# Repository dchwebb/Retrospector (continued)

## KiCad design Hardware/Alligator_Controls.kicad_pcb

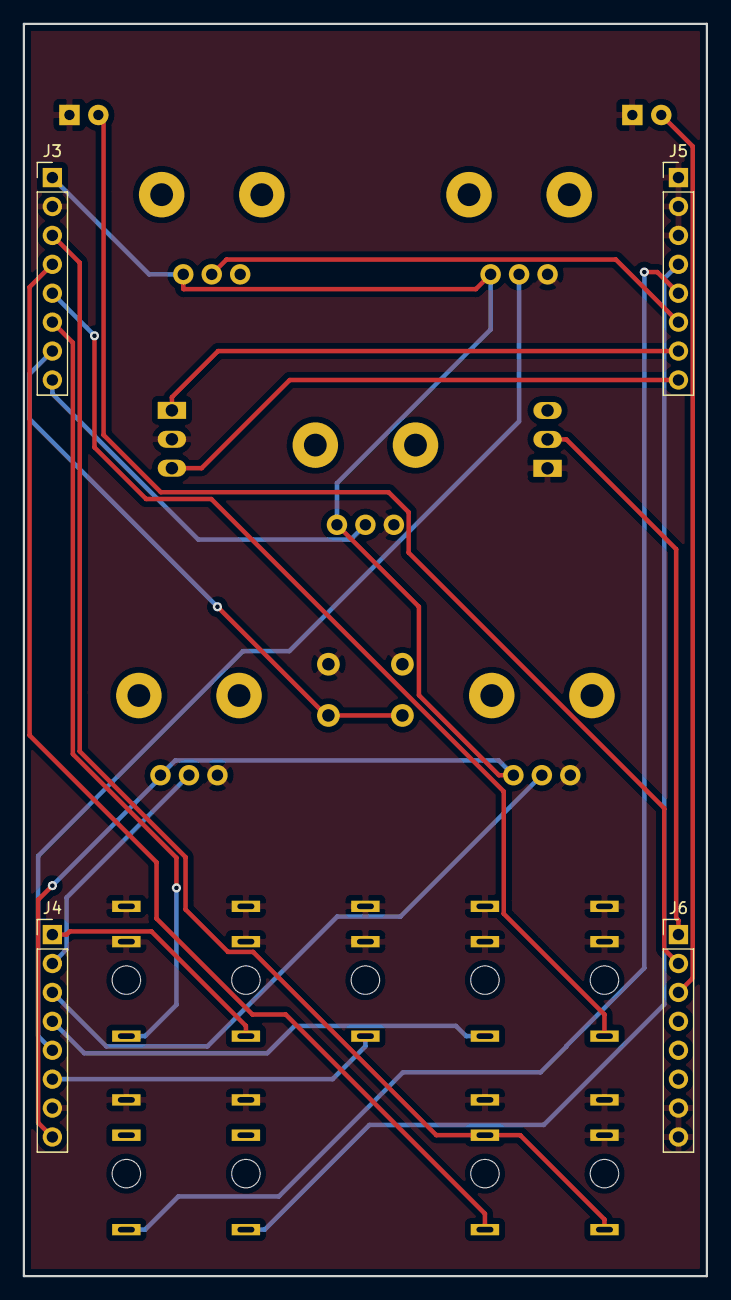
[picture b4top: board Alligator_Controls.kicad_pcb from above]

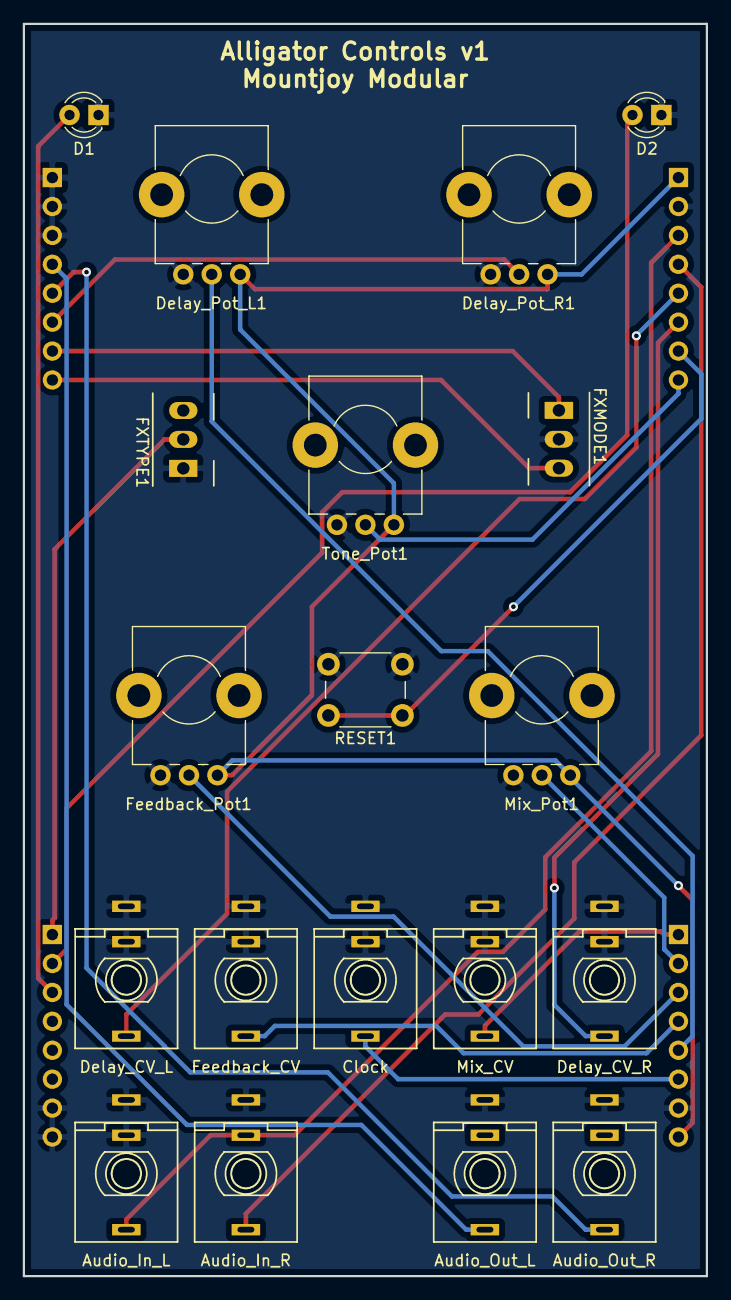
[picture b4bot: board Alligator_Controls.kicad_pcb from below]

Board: 2 copper layers, 60.0 x 110.0 mm, 23 parts (19 on the bottom side), 22 nets.

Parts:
D1, D2: LED; LED_D3.0mm
Delay_Pot_L1: A10k; Alpha_9mm_Potentiometer
Delay_Pot_R1: A10k; Alpha_9mm_Potentiometer
FXMODE1: SW_SPDT_MSM; SPDTSubMiniature
FXTYPE1: SW_SPST; SPDTSubMiniature
Feedback_Pot1: A10k; Alpha_9mm_Potentiometer
J1: Audio_In_L; THONKICONN_hole
J2: Delay_CV_L; THONKICONN_hole
J3, J4, J5, J6: Conn_01x08_Female; Socket_Strip_Straight_1x08_Pitch2.54mm
J7: Mix_CV; THONKICONN_hole
J8: Delay_CV_R; THONKICONN_hole
J9: Clock; THONKICONN_hole
J10: Feedback_CV; THONKICONN_hole
J11: Audio_In_R; THONKICONN_hole
J12: Audio_Out_R; THONKICONN_hole
J13: Audio_Out_L; THONKICONN_hole
Mix_Pot1: A10k; Alpha_9mm_Potentiometer
RESET1: SW_Push; SW_PUSH_6mm
Tone_Pot1: A10k; Alpha_9mm_Potentiometer

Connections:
+3.3VA: Delay_Pot_L1.1, Delay_Pot_R1.1, Feedback_Pot1.1, J3.1, J4.8, Mix_Pot1.1, Tone_Pot1.1
/CLOCK: J4.6, J9.3
/DELAY_CHORUS: FXTYPE1.2, J6.1
/DELAY_CV_L: J2.3, J3.5
/DELAY_CV_R: J3.6, J8.3
/DELAY_POT_L: Delay_Pot_L1.2, J4.5
/DELAY_POT_R: Delay_Pot_R1.2, J5.6
/EXT_AUDIO_IN_L: J1.3, J3.3, J11.2
/EXT_AUDIO_IN_R: J3.4, J11.3
/EXT_AUDIO_OUT_L: J5.4, J13.3
/EXT_AUDIO_OUT_R: J5.5, J12.3
/FEEDBACK_CV: J4.4, J10.3
/FEEDBACK_POT: Feedback_Pot1.2, J4.3
/LED1: D1.2, J6.3
/LED2: D2.2, J6.2
/MIX_CV: J4.1, J7.3
/MIX_POT: J4.2, Mix_Pot1.2
/MODE1: FXMODE1.1, J5.7
/MODE2: FXMODE1.3, J5.8
/RESET: J3.7, RESET1.1
/TONE_POT: J3.8, Tone_Pot1.2
GND: D1.1, D2.1, Delay_Pot_L1.3, Delay_Pot_R1.3, FXMODE1.2, FXTYPE1.1, Feedback_Pot1.3, J1.1, J1.2, J2.1, J2.2, J3.2, J4.7, J5.1, J5.2, J5.3, J6.7, J6.8, J7.1, J7.2, J8.1, J8.2, J9.1, J9.2, J10.1, J10.2, J11.1, J12.1, J13.1, Mix_Pot1.3, RESET1.2, Tone_Pot1.3

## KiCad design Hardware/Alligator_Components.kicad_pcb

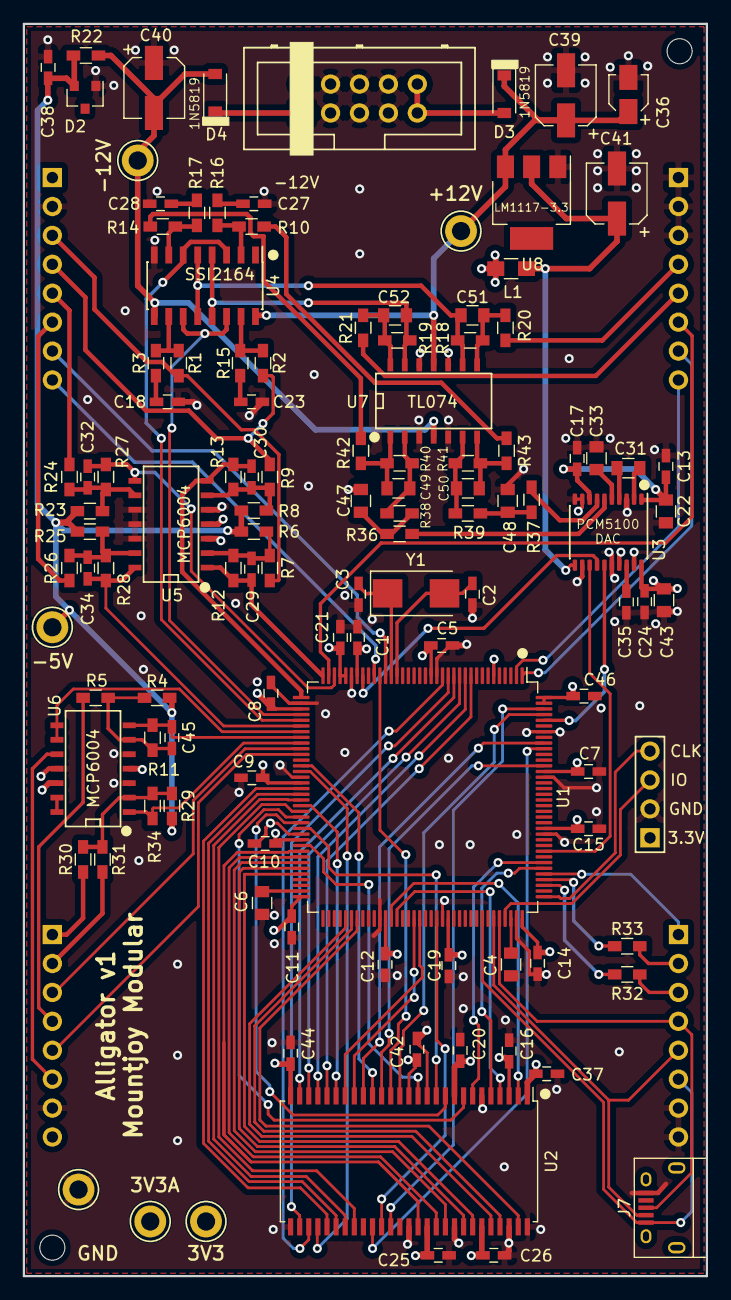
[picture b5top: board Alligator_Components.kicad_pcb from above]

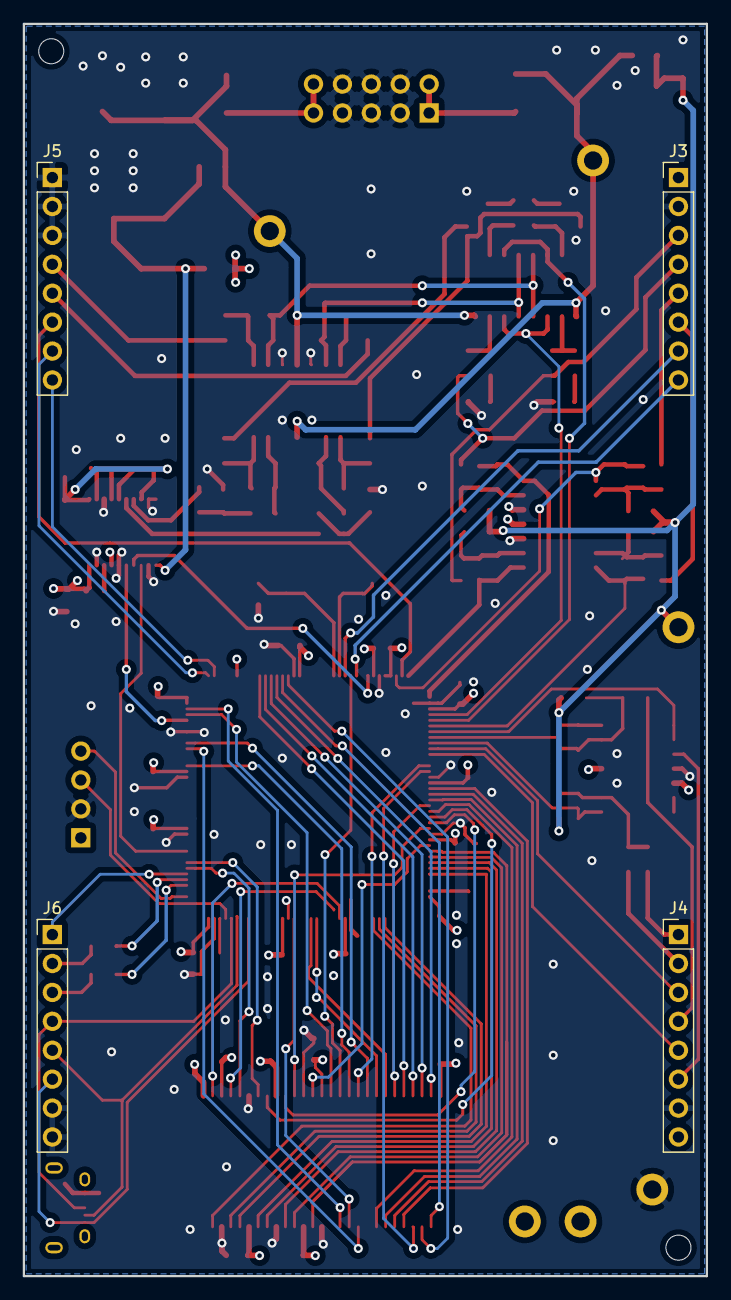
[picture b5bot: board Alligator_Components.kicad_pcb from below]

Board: 4 copper layers, 60.0 x 110.0 mm, 122 parts (4 on the bottom side), 122 nets.

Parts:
C1, C5, C7, C8, C9, C10, C11, C12, C13, C14, C15, C16, C17, C19, C20, C21, C24, C25, C26, C35, C37, C38, C42, C44, C46: 100nF; C_0603_HandSoldering
C2, C3: 30pF; C_0603_HandSoldering
C4, C6, C31, C33: 2.2uF; C_0805
C18, C23, C27, C28: 560pF; C_0603_HandSoldering
C22, C43: 10uF; C_0805
C29, C30, C32, C34, C45: 1.5nF; C_0603_HandSoldering
C36: 10uF; CP_Elec_3x5.3
C39, C40: 22uF; CP_Elec_5x5.3
C41: 47uF; CP_Elec_5x5.3
C47, C48: 1nF; C_0805
C49, C50, C51, C52: 100pF; C_0805
D2: LM4040DBZ-5; SOT-23
D3, D4: 1N5819; D_SOD-123
H1, H2: JLC_Tooling_Hole; JLC_SMT_Tooling_Hole
J1: SWD_Header; SWD_header
J2: Eurorack_10_pin_power; Eurorack_10_pin_header
J3, J4, J5, J6: Conn_01x08_Male; Pin_Header_Straight_1x08_Pitch2.54mm
J7: USB_B_Micro; USB_Micro-B_Amphenol
L1: L; L_0805_HandSoldering
R1, R2, R10, R14, R18, R19: 30k; R_0603_HandSoldering
R3, R15, R16, R17: 510R; R_0603_HandSoldering
R4, R30: 91k; R_0603_HandSoldering
R5, R24, R26: 100k; R_0603_HandSoldering
R6, R8: 20k; R_0603_HandSoldering
R7, R9, R27, R28, R31, R34: 47k; R_0603_HandSoldering
R11: 56k; R_0603_HandSoldering
R12, R13: 6k8; R_0603_HandSoldering
R20, R21, R42, R43: 1k; R_0603_HandSoldering
R22, R36, R37: 2k2; R_0603_HandSoldering
R23, R25: 68k; R_0603_HandSoldering
R29: 75k; R_0603_HandSoldering
R32, R33: 330R; R_0603_HandSoldering
R38, R39: 10k; R_0603_HandSoldering
R40, R41: 33k; R_0603_HandSoldering
TP1, TP2, TP3, TP4, TP5, TP6: TestPoint; Test_Point_Keystone_5005-5009_Compact
U1: STM32H743ZITx; LQFP-144_20x20mm_P0.5mm
U2: IS42S16400J-xC; TSOP-II-54_22.2x10.16mm_P0.8mm
U3: PCM5100APW; SSOP-20_4.4x6.5mm_Pitch0.65mm_Round_Pads
U4: SSI2164; SOIC-16_3.9x9.9mm_Pitch1.27mm
U5, U6: MCP6004; SOIC-14_N
U7: TL074; SOIC-14_N
U8: LM1117-3.3; SOT-223
Y1: 8MHz 20pF; Crystal_SMD_0603-2pin_6.0x3.5mm_HandSoldering

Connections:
+3.3VA: C13.1, C17.1, C21.2, C22.1, J3.1, J4.8, L1.1, TP3.1, U1.32, U1.33, U3.1, U3.8, U5.4, U6.4, U6.12
+3V3: C1.2, C5.2, C7.2, C8.2, C9.2, C10.2, C11.2, C12.2, C14.2, C15.2, C16.2, C19.2, C20.2, C24.1, C25.2, C26.2, C37.2, C41.1, C42.2, C43.1, C44.2, C46.2, J1.1, L1.2, TP2.1, U1.6, U1.17, U1.30, U1.39, U1.52, U1.62, U1.72, U1.84, U1.95, U1.108, U1.121, U1.131, U1.143, U1.144, U2.1, U2.3, U2.9, U2.14, U2.27, U2.43, U2.49, U3.11, U3.17, U3.20, U8.2
+12V: D3.2, J2.9, J2.10
-12V: D4.1, J2.1, J2.2
/AUDIO_IN_L: C29.1, R12.1, U1.36, U5.1
/AUDIO_IN_R: C30.1, R13.1, U1.37, U5.7
/CLOCK: J4.6, U6.10
/CLOCK_SCALED: U1.43, U6.8, U6.9
/DAC_BCLK: U1.117, U3.13
/DAC_DATA: U1.29, U3.14
/DAC_LRCLK: U1.140, U3.15
/DAC_OUT_AMP_L: R14.2, R42.1
/DAC_OUT_AMP_R: R10.2, R43.1
/DAC_OUT_L: R36.2, U3.6
/DAC_OUT_R: R37.2, U3.7
/DELAY_CHORUS: J6.1, U1.113
/DELAY_CV_L: J3.5, R24.2
/DELAY_CV_R: J3.6, R26.2
/DELAY_CV_SCALED_L: C32.1, R27.1, U1.34, U5.8
/DELAY_CV_SCALED_R: C34.1, R28.1, U1.42, U5.14
/DELAY_POT_L: J4.5, U1.47
/DELAY_POT_R: J5.6, U1.35
/DRY_OUT_L: C51.2, R18.2, U4.5, U4.12, U7.9
/DRY_OUT_R: C52.2, R19.2, U4.4, U4.13, U7.13
/EXT_AUDIO_IN_L: J3.3, R1.2, R7.2
/EXT_AUDIO_IN_R: J3.4, R2.2, R9.2
/EXT_AUDIO_OUT_L: J5.4, R20.1
/EXT_AUDIO_OUT_R: J5.5, R21.1
/FEEDBACK_CV: J4.4, R5.2
/FEEDBACK_CV_SCALED: C45.1, R11.1, U1.44, U6.7
/FEEDBACK_POT: J4.3, U1.46
/FMC_A0: U1.10, U2.23
/FMC_A1: U1.11, U2.24
/FMC_A2: U1.12, U2.25
/FMC_A3: U1.13, U2.26
/FMC_A4: U1.14, U2.29
/FMC_A5: U1.15, U2.30
/FMC_A6: U1.50, U2.31
/FMC_A7: U1.53, U2.32
/FMC_A8: U1.54, U2.33
/FMC_A9: U1.55, U2.34
/FMC_A10: U1.56, U2.22
/FMC_A11: U1.57, U2.35
/FMC_BA0: U1.89, U2.20
/FMC_BA1: U1.90, U2.21
/FMC_D0: U1.85, U2.2
/FMC_D1: U1.86, U2.4
/FMC_D2: U1.114, U2.5
/FMC_D3: U1.115, U2.7
/FMC_D4: U1.58, U2.8
/FMC_D5: U1.59, U2.10
/FMC_D6: U1.60, U2.11
/FMC_D7: U1.63, U2.13
/FMC_D8: U1.64, U2.42
/FMC_D9: U1.65, U2.44
/FMC_D10: U1.66, U2.45
/FMC_D11: U1.67, U2.47
/FMC_D12: U1.68, U2.48
/FMC_D13: U1.77, U2.50
/FMC_D14: U1.78, U2.51
/FMC_D15: U1.79, U2.53
/FMC_SDCKE1: U1.135, U2.37
/FMC_SDCLK: U1.93, U2.38
/FMC_SD~E1: U1.136, U2.19
/FMC_SD~WE: U1.26, U2.16
/FMC_~BL0: U1.141, U2.15
/FMC_~BL1: U1.142, U2.39
/FMC_~CAS: U1.132, U2.17
/FMC_~RAS: U1.49, U2.18
/LED1: J6.3, R32.1
/LED2: J6.2, R33.1
/MIX_CV: J4.1, R30.2
/MIX_DRY_CTL: U1.40, U4.11, U4.14
/MIX_POT: J4.2, R31.2
/MIX_WET_CTL: U1.41, U4.3, U4.6
/MODE1: J5.7, U1.1
/MODE2: J5.8, U1.2
/RESET: J3.7, U1.25
/SWCLK: J1.4, U1.109
/SWIO: J1.3, U1.105
/TONE_POT: J3.8, U1.27
/USB_DM: J6.5, J7.2, U1.103
/USB_DP: J6.4, J7.3, U1.104
/USB_VBUS: J6.6, J7.1, U1.101
/WET_DRY_MIX: R34.1, U1.45, U6.1
AREF_-5: C38.1, D2.2, R4.2, R6.2, R8.2, R22.2, R23.2, R25.2, R29.2, TP4.1
GND: C1.1, C2.2, C3.2, C4.2, C5.1, C6.2, C7.1, C8.1, C9.1, C10.1, C11.1, C12.1, C13.2, C14.1, C15.1, C16.1, C17.2, C18.2, C19.1, C20.1, C21.1, C22.2, C23.2, C24.2, C25.1, C26.1, C27.2, C28.2, C33.2, C35.1, C36.2, C37.1, C38.2, C39.2, C40.1, C41.2, C42.1, C43.2, C44.1, C46.1, C47.2, C48.2, D2.1, J1.2, J2.3, J2.4, J2.5, J2.6, J2.7, J2.8, J3.2, J4.7, J5.1, J5.2, J5.3, J6.7, J6.8, J7.5, TP1.1, U1.16, U1.31, U1.38, U1.51, U1.61, U1.83, U1.94, U1.107, U1.120, U1.130, U1.138, U2.6, U2.12, U2.28, U2.41, U2.46, U2.52, U2.54, U3.3, U3.9, U3.10, U3.12, U3.16, U3.19, U4.8, U5.3, U5.5, U5.10, U5.11, U5.12, U6.3, U6.5, U6.11, U7.3, U7.5, U7.10, U7.12, U8.1
unnamed: C2.1, U1.23, Y1.2
unnamed: C3.1, U1.24, Y1.1
unnamed: C4.1, U1.106
unnamed: C6.1, U1.71
unnamed: C18.1, R3.1
unnamed: C23.1, R15.1
unnamed: C27.1, R16.1
unnamed: C28.1, R17.1
unnamed: C29.2, R6.1, R7.1, R12.2, U5.2
unnamed: C30.2, R8.1, R9.1, R13.2, U5.6
unnamed: C31.1, U3.2
unnamed: C31.2, U3.4
unnamed: C32.2, R23.1, R24.1, R27.2, U5.9
unnamed: C33.1, U3.5
unnamed: C34.2, R25.1, R26.1, R28.2, U5.13
unnamed: C35.2, U3.18
unnamed: C45.2, R4.1, R5.1, R11.2, U6.6
unnamed: C47.1, R36.1, R38.2
unnamed: C48.1, R37.1, R39.2
unnamed: C49.1, R40.1, R42.2, U7.1
unnamed: C49.2, R38.1, R40.2, U7.2
unnamed: C50.1, R41.1, R43.2, U7.7
unnamed: C50.2, R39.1, R41.2, U7.6
unnamed: C51.1, R18.1, R20.2, U7.8
unnamed: C52.1, R19.1, R21.2, U7.14
unnamed: R1.1, R3.2, U4.10
unnamed: R10.1, R16.2, U4.2
unnamed: R14.1, R17.2, U4.7
unnamed: R2.1, R15.2, U4.15
unnamed: R29.1, R30.1, R31.1, R34.2, U6.2
unnamed: R32.2, U1.111
unnamed: R33.2, U1.112
unnamed: U6.13, U6.14
VCC: C36.1, C39.1, D3.1, TP5.1, U4.16, U7.11, U8.3
VEE: C40.2, D4.2, R22.1, TP6.1, U4.9, U7.4

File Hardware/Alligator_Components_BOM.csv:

"Comment","Designator","Footprint","LCSC Part #"
"100nF","C1, C5, C7, C8, C9, C10, C11, C12, C13, C14, C15, C16, C17, C19, C20, C21, C24, C25, C26, C35, C37, C38, C42, C44, C46, ","C_0603_HandSoldering","C14663"
"30pF","C2, C3, ","C_0603_HandSoldering","C22397"
"2.2uF","C4, C6, C31, C33, ","C_0805","C49217"
"560pF","C18, C23, C27, C28, ","C_0603_HandSoldering","C84721"
"10uF","C22, C43, ","C_0805","C15850 "
"1.5nF","C29, C30, C32, C34, C45, ","C_0603_HandSoldering","C1595"
"10uF","C36, ","CP_Elec_3x5.3","C249452"
"47uF","C41, ","CP_Elec_5x5.3","C134798"
"1nF","C47, C48, ","C_0805","C46653 "
"100pF","C49, C50, C51, C52, ","C_0805","C1790 "
"LM4040DBZ-5","D2, ","SOT-23","C69316"
"1N5819","D3, D4, ","D_SOD-123","C169540"
"L","L1, ","L_0805_HandSoldering","C1046"
"30k","R1, R2, R10, R14, R18, R19, ","R_0603_HandSoldering","C22984"
"510R","R3, R15, R16, R17, ","R_0603_HandSoldering","C23193"
"91k","R4, R30, ","R_0603_HandSoldering","C23265"
"100k","R5, R24, R26, ","R_0603_HandSoldering","C25803"
"20k","R6, R8, ","R_0603_HandSoldering","C4184 "
"47k","R7, R9, R27, R28, R31, R34, ","R_0603_HandSoldering","C25819"
"56k","R11, ","R_0603_HandSoldering","C23206"
"6k8","R12, R13, ","R_0603_HandSoldering","C23212 "
"1k","R20, R21, R42, R43, ","R_0603_HandSoldering","C21190"
"2k2","R22, R36, R37, ","R_0603_HandSoldering","C4190"
"68k","R23, R25, ","R_0603_HandSoldering","C23231"
"75k","R29, ","R_0603_HandSoldering","C23242 "
"330R","R32, R33, ","R_0603_HandSoldering","C23138"
"10k","R38, R39, ","R_0603_HandSoldering","C25804"
"33k","R40, R41, ","R_0603_HandSoldering","C4216 "
"STM32H743ZITx","U1, ","LQFP-144_20x20mm_P0.5mm","C114408"
"IS42S16400J-xC","U2, ","TSOP-II-54_22.2x10.16mm_P0.8mm","C69411"
"PCM5100APW","U3, ","SSOP-20_4.4x6.5mm_Pitch0.65mm_Round_Pads","C131154"
"MCP6004","U5, U6, ","SOIC-14_N","C7378"
"TL074","U7, ","SOIC-14_N","C6964"
"LM1117-3.3","U8, ","SOT-223","C6186"

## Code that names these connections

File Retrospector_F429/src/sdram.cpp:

#include <stdint.h>
#include "sdram.h"
#include "initialisation.h"

// SDRAM attached to bank 2 (ie use FMC_SDCKE1 and FMC_SDNE1 rather than 0 equivalents)

/*-- GPIOs Configuration - use Alternate Function 12
 +-------------------+--------------------+--------------------+--------------------+
 +                       SDRAM pins assignment                                      +
 +-------------------+--------------------+--------------------+--------------------+
 | PD0  <-> FMC_D2   | PE0  <-> FMC_NBL0  | PF0  <-> FMC_A0    | PG0  <-> FMC_A10   |
 | PD1  <-> FMC_D3   | PE1  <-> FMC_NBL1  | PF1  <-> FMC_A1    | PG1  <-> FMC_A11   |
 | PD8  <-> FMC_D13  | PE7  <-> FMC_D4    | PF2  <-> FMC_A2    | PG4  <-> FMC_BA0   |
 | PD9  <-> FMC_D14  | PE8  <-> FMC_D5    | PF3  <-> FMC_A3    | PG5  <-> FMC_BA1   |
 | PD10 <-> FMC_D15  | PE9  <-> FMC_D6    | PF4  <-> FMC_A4    | PG8  <-> FMC_SDCLK |
 | PD14 <-> FMC_D0   | PE10 <-> FMC_D7    | PF5  <-> FMC_A5    | PG15 <-> FMC_NCAS  |
 | PD15 <-> FMC_D1   | PE11 <-> FMC_D8    | PF11 <-> FMC_NRAS  |--------------------+
 +-------------------| PE12 <-> FMC_D9    | PF12 <-> FMC_A6    |
                     | PE13 <-> FMC_D10   | PF13 <-> FMC_A7    |
                     | PE14 <-> FMC_D11   | PF14 <-> FMC_A8    |
                     | PE15 <-> FMC_D12   | PF15 <-> FMC_A9    |
 +-------------------+--------------------+--------------------+
 | PB5 <-> FMC_SDCKE1|
 | PB6 <-> FMC_SDNE1 |
 | PC0 <-> FMC_SDNWE |
 +-------------------+
*/

void InitRamPin(GPIO_TypeDef* bank, std::initializer_list<uint8_t> pins) {
	for (auto pin : pins) {
		// Set the output speed to highest
		bank->OSPEEDR |= (0b10 << (2 * pin));		// NB 0b11 for H473

		// Set GPIO mode to alternate function (00: Input (reset state)	01: General purpose output mode	10: Alternate function mode	11: Analog mode)
		bank->MODER |= (0b10 << (2 * pin));
		bank->MODER &= ~(0b01 << (2 * pin));

		// Set alternate function to AF12
		if (pin < 8)
			bank->AFR[0] |= 12 << (4 * pin);
		else
			bank->AFR[1] |= 12 << (4 * (pin - 8));
	}
}

void InitSDRAM(void) {

	// Initialise clock for SDRAM pins
	RCC->AHB1ENR |= RCC_AHB1ENR_GPIOBEN;
	RCC->AHB1ENR |= RCC_AHB1ENR_GPIOCEN;
	RCC->AHB1ENR |= RCC_AHB1ENR_GPIODEN;
	RCC->AHB1ENR |= RCC_AHB1ENR_GPIOEEN;
	RCC->AHB1ENR |= RCC_AHB1ENR_GPIOFEN;
	RCC->AHB1ENR |= RCC_AHB1ENR_GPIOGEN;

	InitRamPin(GPIOB, {5, 6});
	InitRamPin(GPIOC, {0});
	InitRamPin(GPIOD, {0, 1, 8, 9, 10, 14, 15});
	InitRamPin(GPIOE, {0, 1, 7, 8, 9, 10, 11, 12, 13, 14, 15});
	InitRamPin(GPIOF, {0, 1, 2, 3, 4, 5, 11, 12, 13, 14, 15});
	InitRamPin(GPIOG, {0, 1, 4, 5, 8, 15});

	// Enable the SDRAM Controller
	RCC->AHB3ENR |= RCC_AHB3ENR_FMCEN;
	while (FMC_Bank5_6->SDSR & FMC_SDSR_BUSY_Msk);

	// Clock configuration - FMC clock (fmc_ker_ck) selected with RCC_D1CCIPR_FMCSEL register. Defaults to D1 domain AHB prescaler (RCC_D1CFGR_HPRE_3) ie main clock /2 = 140MHz
	//RCC->D1CCIPR |= RCC_D1CCIPR_FMCSEL_1;					// 10: pll2_r_ck clock selected as kernel peripheral clock (286MHz)

	// Memory maximum clock speed is 140MHz at CAS latency = 3

	// SDCLK, RPIPE, RBURST in Control register and TRP, TRC in Timing register are shared and must be configured against bank 1 even though using bank 2
	FMC_Bank5_6->SDCR[0] = FMC_SDCR1_RPIPE_0 |				// Read pipe: 01: One HCLK clock cycle delay
			               FMC_SDCR1_RBURST |				// Burst read: 1: single read requests are always managed as bursts
	                       FMC_SDCR1_SDCLK_1;				// SDRAM clock configuration 10: SDCLK period = 2 x HCLK periods (@180MHz = 5.55ns period; 2 x period = 11.1ns)

	FMC_Bank5_6->SDCR[1] = FMC_SDCR2_CAS_Msk |				// CAS Latency in number of memory clock cycles: 11: 3 cycles
	                       FMC_SDCR2_NB |					// Number of internal banks: 1: Four internal Banks (2M x16 x4 Banks)
	                       FMC_SDCR2_MWID_0 |				// Memory data bus width.	00: 8 bits	01: 16 bits	10: 32 bits
	                       FMC_SDCR2_NR_0 |					// Number of row address bits 01: 12 bits = 4096 - See RAM datasheet p2 Device Overview
						   FMC_SDCR2_NC_0;					// Number of column address bits 01: 9 bits = 512

	// ISSI IS42S16800 SDRAM Timings on p17 of datasheet. All settings below in cycles minus one
	FMC_Bank5_6->SDTR[0] = 2 << FMC_SDTR1_TRP_Pos |			// Row precharge delay - requires 15ns (3 cycles)
	                       5 << FMC_SDTR1_TRC_Pos;			// Row Cycle Delay - requires 60ns (6 cycles) in data sheet: trc Command Period (REF to REF / ACT to ACT)

	FMC_Bank5_6->SDTR[1] = 2 << FMC_SDTR2_TRCD_Pos |		// Row to column delay - requires 15ns (3 cycles)
	                       2 << FMC_SDTR2_TWR_Pos |			// Write Recovery Time - requires 14ns (3 cycles) - in dataheet Input Data To Precharge/Command Delay time
	                       3 << FMC_SDTR2_TRAS_Pos |		// Self Refresh Time - minimum 37ns (4 cycles)
	                       6 << FMC_SDTR2_TXSR_Pos |		// Exit Self Refresh Time - 67ns (7 cycles)
	                       2 << FMC_SDTR2_TMRD_Pos;			// Load to Active Delay - requires 14ns (3 cycles)

	// p1664  Set MODE to 001 and configure Target Bank 2 to start delivering the clock to the memory (SDCKE is driven high)
	while (FMC_Bank5_6->SDSR & FMC_SDSR_BUSY_Msk);
	FMC_Bank5_6->SDCMR = FMC_SDCMR_CTB2 | 0b001 << FMC_SDCMR_MODE_Pos;		// Command target bank 2 | Clock enable command

	// sleep at least 100uS
	uint32_t time = SysTickVal;
	while (time == SysTickVal) {};

	// Set MODE to 010 and configure Target Bank 2 to issue a "Precharge All" command
	while (FMC_Bank5_6->SDSR & FMC_SDSR_BUSY_Msk);
	FMC_Bank5_6->SDCMR = FMC_SDCMR_CTB2 | 0b010 << FMC_SDCMR_MODE_Pos;		// Command target bank 2 | Precharge All command

	// Set MODE to 011 to configure number of consecutive Auto-refresh commands (NRFS) in the FMC_SDCMR register. Typical number is 8
	while (FMC_Bank5_6->SDSR & FMC_SDSR_BUSY_Msk);
	FMC_Bank5_6->SDCMR = FMC_SDCMR_CTB2 |					// Command target bank (bank 2)
						 0b011 << FMC_SDCMR_MODE_Pos |		// Auto refresh command
						 3 << FMC_SDCMR_NRFS_Pos;			// Number of auto-refresh less one (ie 4)

	// These parameters are specified in the SDRAM datasheet (p19 for ISSI SDRAM)
	#define SDRAM_MODE_BURST_LENGTH_1				((uint16_t)0x0000)
	#define SDRAM_MODE_BURST_LENGTH_2				((uint16_t)0x0001)
	#define SDRAM_MODE_BURST_LENGTH_4				((uint16_t)0x0002)
	#define SDRAM_MODE_BURST_LENGTH_8				((uint16_t)0x0004)
	#define SDRAM_MODE_BURST_TYPE_SEQUENTIAL		((uint16_t)0x0000)
	#define SDRAM_MODE_BURST_TYPE_INTERLEAVED		((uint16_t)0x0008)
	#define SDRAM_MODE_CAS_LATENCY_2				((uint16_t)0x0020)
	#define SDRAM_MODE_CAS_LATENCY_3				((uint16_t)0x0030)
	#define SDRAM_MODE_OPERATING_MODE_STANDARD		((uint16_t)0x0000)
	#define SDRAM_MODE_WRITEBURST_MODE_PROGRAMMED	((uint16_t)0x0000)
	#define SDRAM_MODE_WRITEBURST_MODE_SINGLE		((uint16_t)0x0200)

	// Set MODE to 100 to issue a "Load Mode Register" command in order to program the SDRAM
	uint32_t tr_tmp = SDRAM_MODE_BURST_LENGTH_4 |		// was SDRAM_MODE_BURST_LENGTH_2
				SDRAM_MODE_BURST_TYPE_SEQUENTIAL |
				SDRAM_MODE_CAS_LATENCY_3 |
				SDRAM_MODE_OPERATING_MODE_STANDARD |
				SDRAM_MODE_WRITEBURST_MODE_SINGLE;

	while (FMC_Bank5_6->SDSR & FMC_SDSR_BUSY_Msk);
	FMC_Bank5_6->SDCMR = FMC_SDCMR_CTB2 |					// Command target bank (bank 2)
						 0b100 << FMC_SDCMR_MODE_Pos |		// Clock enable command
						 tr_tmp << FMC_SDCMR_MRD_Pos;		// Mode register direction

	// Set the refresh counter to trigger an auto refresh often enough to prevent data loss.
	FMC_Bank5_6->SDRTR = 683 << FMC_SDRTR_COUNT_Pos;

	// 16 megabytes of ram now available at address 0xD0000000 - 0xD1000000
}

// SDRAM testing variables
using memSize = uint32_t;
uint32_t testAddr;
memSize* tempAddr;
constexpr uint32_t maxAddr = 0x1000000 / sizeof(memSize);
uint32_t MemTestDuration;
uint32_t MemTestCount = 0;
uint32_t MemTestErrors = 0;

// Tell linker script to store buffer in SDRAM
uint32_t __attribute__((section (".sdramSection"))) SDRAMBuffer[maxAddr];

// Test SDRAM
void MemoryTest() {
	static uint32_t memErrs = 0;
	uint32_t testStart = SysTickVal;

	// Blank Memory
	GPIOC->ODR |= GPIO_ODR_OD11;			// Toggle LED for testing
	for (testAddr = 0; testAddr < maxAddr; ++testAddr) {
		tempAddr = (memSize *)(0xD0000000 + (testAddr * sizeof(memSize)));
		*tempAddr = 0;
	}
	GPIOC->ODR &= ~GPIO_ODR_OD11;

	// Write
	for (testAddr = 0; testAddr < maxAddr; ++testAddr) {
		tempAddr = (memSize *)(0xD0000000 + (testAddr * sizeof(memSize)));
		*tempAddr = static_cast<memSize>(testAddr);

	}

	// Read
	for (testAddr = 0; testAddr < maxAddr; ++testAddr) {
		memSize val = SDRAMBuffer[testAddr];
		if (val != static_cast<memSize>(testAddr))
			++memErrs;
	}

	// H743: For 32 bit words > 6632 using PLL2 at 143MHz, 6309 at 220MHz, 6385 (2813 with DCache, 2347 with DCache and ICache) at 100MHz
	// F429: 32 bit words: 180MHz 2975

	MemTestDuration = SysTickVal - testStart;
	++MemTestCount;
	MemTestErrors = memErrs;
}

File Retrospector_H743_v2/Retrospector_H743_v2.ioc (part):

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Mcu.Name=STM32H743ZITx
Mcu.Package=LQFP144
Mcu.UserName=STM32H743ZITx
PA11.Mode=Device_Only
PA11.Signal=USB_OTG_FS_DM
PA12.Mode=Device_Only
PA12.Signal=USB_OTG_FS_DP
PA4.Signal=ADCx_INP18
PA5.Signal=COMP_DAC12_group
PA7.Signal=FMC_SDNWE
PA8.Mode=Activate_SOF_FS
PA8.Signal=USB_OTG_FS_SOF
PA9.Mode=Activate_VBUS
PA9.Signal=USB_OTG_FS_VBUS
PB0.GPIOParameters=GPIO_Label
PB0.GPIO_Label=LD1 [Green Led]
PB0.Signal=GPIO_Output
PB13.Mode=Half_Duplex_Master_Tx
PB13.Signal=I2S2_CK
PB14.GPIOParameters=GPIO_Label
PB14.GPIO_Label=LD3 [Red Led]
PB14.Signal=GPIO_Output
PB15.Mode=Half_Duplex_Master_Tx
PB15.Signal=I2S2_SDO
PB5.Mode=SdramChipSelect2_2
PB5.Signal=FMC_SDCKE1
PB6.Mode=SdramChipSelect2_2
PB6.Signal=FMC_SDNE1
PB7.GPIOParameters=GPIO_Pu
PB7.GPIO_Pu=GPIO_PULLUP
PB7.Mode=I2C
PB7.Signal=I2C1_SDA
PB8.GPIOParameters=GPIO_Pu
PB8.GPIO_Pu=GPIO_PULLUP
PB8.Mode=I2C
PB8.Signal=I2C1_SCL
PB9.Mode=Half_Duplex_Master_Tx
PB9.Signal=I2S2_WS
PC0.Signal=ADCx_INP10
PC13.GPIOParameters=GPIO_Label
PC13.GPIO_Label=B1 [Blue PushButton]
PC13.Signal=GPIO_Input
PC14-OSC32_IN\ (OSC32_IN).Mode=LSE-External-Oscillator
PC14-OSC32_IN\ (OSC32_IN).Signal=RCC_OSC32_IN
PC15-OSC32_OUT\ (OSC32_OUT).Mode=LSE-External-Oscillator
PC15-OSC32_OUT\ (OSC32_OUT).Signal=RCC_OSC32_OUT
PD0.Signal=FMC_D2_DA2
PD1.Signal=FMC_D3_DA3
PD10.Signal=FMC_D15_DA15
PD14.Signal=FMC_D0_DA0
PD15.Signal=FMC_D1_DA1
PD8.Signal=FMC_D13_DA13
PD9.Signal=FMC_D14_DA14
PE0.Signal=FMC_NBL0
PE1.Signal=FMC_NBL1
PE10.Signal=FMC_D7_DA7
PE11.Signal=FMC_D8_DA8
PE12.Signal=FMC_D9_DA9
PE13.Signal=FMC_D10_DA10
PE14.Signal=FMC_D11_DA11
PE15.Signal=FMC_D12_DA12
PE7.Signal=FMC_D4_DA4
PE8.Signal=FMC_D5_DA5
PE9.Signal=FMC_D6_DA6
PF0.Signal=FMC_A0
PF1.Signal=FMC_A1
PF11.Signal=FMC_SDNRAS
PF12.Signal=FMC_A6
PF13.Signal=FMC_A7
PF14.Signal=FMC_A8
PF15.Signal=FMC_A9
PF2.Signal=FMC_A2
PF3.Signal=FMC_A3
PF4.Signal=FMC_A4
PF5.Signal=FMC_A5
PF7.Mode=TX_Only_Simplex_Unidirect_Master
PF7.Signal=SPI5_SCK
PF9.Mode=TX_Only_Simplex_Unidirect_Master
PF9.Signal=SPI5_MOSI
PG0.Signal=FMC_A10
PG1.Signal=FMC_A11
PG15.Signal=FMC_SDNCAS
PG2.Signal=FMC_A12
PG4.Signal=FMC_A14_BA0
PG5.Signal=FMC_A15_BA1
PG7.GPIOParameters=GPIO_Label
PG7.GPIO_Label=USB_OTG_FS_OVCR
PG7.Signal=GPXTI7
PG8.Signal=FMC_SDCLK
PH0-OSC_IN\ (PH0).Mode=HSE-External-Oscillator
PH0-OSC_IN\ (PH0).Signal=RCC_OSC_IN
PH1-OSC_OUT\ (PH1).Mode=HSE-External-Oscillator
PH1-OSC_OUT\ (PH1).Signal=RCC_OSC_OUT
RCC.HSE_VALUE=8000000
RCC.SYSCLKFreq_VALUE=400000000
RCC.SYSCLKSource=RCC_SYSCLKSOURCE_PLLCLK
board=NUCLEO-H743ZI2
boardIOC=true

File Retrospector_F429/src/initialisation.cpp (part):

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
void InitDAC()
{
	// DAC1_OUT2 on PA5
	RCC->AHB1ENR |= RCC_AHB1ENR_GPIOAEN;			// GPIO port clock
	RCC->APB1ENR |= RCC_APB1ENR_DACEN;			// Enable DAC Clock

	DAC->CR |= DAC_CR_EN1;							// Enable DAC using PA4 (DAC_OUT1)
	DAC->CR |= DAC_CR_BOFF1;						// Enable DAC channel output buffer to reduce the output impedance
	DAC->CR |= DAC_CR_TEN1;							// DAC 1 enable trigger
	DAC->CR |= DAC_CR_TSEL1;						// Set trigger to software (0b111: Software trigger)

	DAC->CR |= DAC_CR_EN2;							// Enable DAC using PA5 (DAC_OUT2)
	DAC->CR |= DAC_CR_BOFF2;						// Enable DAC channel output buffer
	DAC->CR |= DAC_CR_TEN2;							// DAC 2 enable trigger
	DAC->CR |= DAC_CR_TSEL2;						// Set trigger to software (0b111: Software trigger)
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
	/*--------------------------------------------------------------------------------------------
	Configure ADC Channels to be converted:
		0	PA2 ADC12_INP14		AUDIO_IN_L
		1	PA3 ADC12_INP15 	AUDIO_IN_R
		2	PC5 ADC12_INP8		WET_DRY_MIX
		3	PB1 ADC12_INP5		DELAY_POT_L
		4	PA1 ADC1_INP17		DELAY_POT_R
		5	PA0 ADC1_INP16		DELAY_CV_SCALED_L
		6	PA6 ADC12_INP3 		DELAY_CV_SCALED_R
		7	PB0 ADC12_INP9		FEEDBACK_POT
		8	PC4 ADC12_INP4		FEEDBACK_CV_SCALED
		9	PC1 ADC123_INP11 	TONE_POT
	*/

	// NB reset mode of GPIO pins is 0b11 = analog mode so shouldn't need to change
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
	/*--------------------------------------------------------------------------------------------
	Configure ADC Channels to be converted:
		0	PA2 ADC12_INP2		AUDIO_IN_L
		1	PA3 ADC12_INP3 		AUDIO_IN_R
		2	PC5 ADC12_INP15		WET_DRY_MIX
		3	PB1 ADC12_INP9		DELAY_POT_L
		4	PA1 ADC1_INP1		DELAY_POT_R
		5	PA0 ADC1_INP0		DELAY_CV_SCALED_L
		6	PA6 ADC12_INP6 		DELAY_CV_SCALED_R
		7	PB0 ADC12_INP8		FEEDBACK_POT
		8	PC4 ADC12_INP14		FEEDBACK_CV_SCALED
		9	PC1 ADC123_INP11 	TONE_POT
	*/
	InitAdcPin(GPIOA, 2, 2);
	InitAdcPin(GPIOA, 3, 3);
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	RCC->AHB1ENR |= RCC_AHB1ENR_GPIODEN;			// GPIO port clock
	RCC->APB1ENR |= RCC_APB1ENR_SPI2EN;

	// PB9: I2S2_WS [alternate function AF5]
	GPIOB->MODER |= GPIO_MODER_MODE9_1;				// 10: Alternate function mode
	GPIOB->AFR[1] |= 5 << GPIO_AFRH_AFSEL9_Pos;		// Alternate Function 5 (I2S2)

	// PD3 I2S2_CK [alternate function AF5]
	GPIOD->MODER |= GPIO_MODER_MODE3_1;				// 00: Input (reset state)	01: General purpose output mode	10: Alternate function mode	11: Analog mode
	GPIOD->AFR[0] |= 5 << GPIO_AFRL_AFSEL3_Pos;		// Alternate Function 5 (I2S2)

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
void InitTempoClock()
{
	// Fire interrupt when clock pulse is received on PA7 - See manual p383
	RCC->AHB1ENR |= RCC_AHB1ENR_GPIOAEN;			// GPIO port clock
	GPIOA->MODER &= ~GPIO_MODER_MODE7_Msk;			// 00: Input mode
	SYSCFG->EXTICR[1] |= SYSCFG_EXTICR2_EXTI7_PA;	// Select Pin PA7 which uses External interrupt 2
	EXTI->RTSR |= EXTI_RTSR_TR7;					// Enable rising edge trigger
	EXTI->IMR |= EXTI_IMR_IM7;					// Activate interrupt using mask register

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{
	// Configure timer to use Capture and Compare mode on external clock to time duration between pulses (not using)

	// FIXME Production will use PA7 - temporarily using PB5 as also configured as TIM3_CH2
	// See manual page 1670 for info on Capture and Compare Input mode
	RCC->AHB1ENR |= RCC_AHB1ENR_GPIOBEN;			// GPIO port clock
	GPIOB->MODER &= ~GPIO_MODER_MODE5_0;			// Alternate function is Mode 0b10 (defaults to 0b11)
	GPIOB->AFR[0] |= 2 << GPIO_AFRL_AFSEL5_Pos;		// Alternate Function 2 for TIM3_CH2 on PB5 and PA7
	RCC->APB1ENR |= RCC_APB1ENR_TIM3EN;
	TIM3->ARR = 65535;
	TIM3->PSC = 2000;
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
void InitLEDs()
{
	// Initialise timing LEDs on PC10 and PC11
	RCC->AHB1ENR |= RCC_AHB1ENR_GPIOCEN;			// GPIO port clock
	GPIOC->MODER |= GPIO_MODER_MODE10_0;			// 00: Input (reset state)	01: General purpose output mode	10: Alternate function mode	11: Analog mode
	GPIOC->MODER |= GPIO_MODER_MODE11_0;			// 00: Input (reset state)	01: General purpose output mode	10: Alternate function mode	11: Analog mode
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
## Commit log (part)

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2020-06-26 First draft of VCOM UART functionality - basics working but RX interrupt not clearing
2020-06-27 Fixed issues switching to high speed mode; USART working
2020-06-28 Provisional ADC code
2020-06-30 Rough first draft of ADC with DMA code (working)
2020-06-30 Added multiple ADC channels and oversampling
2020-07-02 First working draft of I2S DAC controller
2020-07-02 I2S Code working
2020-07-07 Updates to schematic; Output ADC data over I2S via interrupt with L/R awareness
2020-07-08 Basic variable delay implemented
2020-07-09 Preliminary attempts at crossfading when changing delay time
2020-07-10 Refactoring
2020-07-10 Moved delay functionality to digitalDelay class; further working smoothing delay rate transitions
2020-08-18 Added working USB Device code (mainly borrowed from MIDI Monger for testing); also updated UART debugging code
2020-08-21 UART Cleanup
2020-09-03 Attempt to identify zero crossing poinst when changing delay times (too slow)
2020-09-04 Delay change implemented on matching crossing - still not sounding right
2020-09-07 Added initialisation and test code for DAC output; Schematic changes for first attempt at Wet/Dry mixer
2020-09-08 Implemented Wet/Dry mix control using MCU to process curves
2020-09-09 Updates to schematic
2020-09-11 First Draft of Component Schematic Done; Added enum for ADC input selction
2020-09-14 Initial pass at routing MCU and DRAM
2020-09-15 Further routing of PCB
2020-09-17 Further updates to pcb layout
2020-09-18 Error pass of schematic and PCB - power rails still need routing
2020-09-18 Completed PCB routing
2020-09-30 Tooling holes added for SMT assembly; started routing control PCB
2020-10-01 More controls routing
2020-10-01 Control PCB orientation tests
2020-10-06 Renamed project files; work on panel PCB and 3d Models
2020-10-08 Added some test clock code using timer to capture clock interval in capture and compare input mode
2020-10-08 Added Clock on interrupt method
2020-10-15 Final changes to PCBs for manufacture
2020-10-30 Pre-migration to production prototype board
2020-10-31 Updated ADC conversions to match prototype board
2020-11-10 Fixed USB (Enable VDD33USB supply level detector)
2020-11-13 SDRAM working with basic tests
2020-11-13 Memory tests refined to allow easy benchmarking of different word sizes
2020-11-14 Updated SDRAM controller to use PLL2R for clock; moved memory tests to separate routine for timing testing
2020-11-15 Experiments with memory timing (currently working at 100MHz); tests with instruction and data cache; attempt to disable data cache for ADC (not working)
2020-11-16 MPU working correctly - data and instruction cache are enabled generally; data cache disabled for ADC DMA buffer
2020-11-20 Started adding circuitry for Buck conversion
2020-11-22 Added Buck converter to PCB; other layout changes
2020-11-23 Completed draft of rev 2 pcb
2020-11-23 Include inverting op amp output stage so output is not polarity reversed
2020-11-25 Created Power Test Board for TPS5410D
2020-11-25 Initial schematics for power test boards with various chips
2020-12-02 Added project to support STM32F429 using same hardware; all components tested and working except I2S DAC
2020-12-04 STM32F429 hardware support fully working;
    Proper implementation would require all ADC data to be scaled from 16 bit (H743) to 12 bit (F429)
2020-12-04 Minor updates to memory test code
2020-12-15 Debugging DAC clock issues when using FMC to control SDRAM
    Workaround is to switch the clock for the I2S DAC to peripheral clock (also used by ADC at present)
2020-12-16 More clock experiments
2020-12-16 Configure ADC2 so audio and control signals can be processed separately
2020-12-18 Low pass filter controlled from tone knob working using FIR filters (not windowed)
2020-12-19 Implemented basic FIR High pass filter
2020-12-20 Tests for timing of FIR coefficent calculation
2020-12-21 Added option to dump right channel samples; fixed right channel output; fixed optimisation -O1 breaking USB output
2020-12-22 Reduced ADC clock speed to 8.5 cycles to fix issue where ADC readings were 'bleeding' between controls
2020-12-22 Implemented cache of recent samples for fast filter calculation from SRAM
2020-12-27 Implemented preliminary feedback control; experiments smoothing delay times;
    Added volatile directives to prevent delay pots switching L/R
2020-12-28 Added filter window (Kaiser); support for mode switch; better handling for line feeds in CDC; various debug updates
2020-12-29 Better handling of sample overflow; clean up of Window function; general tidy
2020-12-30 Implemented reverse delay; mode switch selectes short, long and long reversed modes
2020-12-30 Added LED delay indication; Fiddling with Filter settings
2020-12-31 Crude tempo clock variable rates implemented (needs work on LEDs, more efficient multiplication level selection)
2021-01-02 Fixes to LED code - still need to handle fractional tempo settings
2021-01-02 Further work on LED handling; started implementing IIR
2021-01-03 In reverse mode LEDs fade in to indicate delay length
2021-01-05 Further work cleaning IIR code and trying to get HP IIR filter to behave correctly
2021-01-06 Further updates to IIR filtering; basically working though still glitching
2021-01-07 Switched to C++17; data moved to DTCMRAM
2021-01-08 Implemented compression routine
2021-01-10 Refactor of filtering code
2021-01-10 Elliptic IIR filter working
2021-01-12 Refactoring and tidying of IIR filter code
2021-01-12 Major refactoring of Filter code
2021-01-12 First stage filter refactor complete: iir filters are self-contained
2021-01-13 Added ability to cleanly restart I2S after debugging caused buffer underrun
2021-01-15 Further updates of IIR LP to HP mode - still glitchy due to phase shifting differences between LP and HP modes
2021-01-15 Further work on filter modes; support CV/Pot control over filter
2021-01-16 Added some prototype ping pong delay mechanism
2021-01-18 Added debug code to identify channel swapping issue
2021-01-18 Sample buffer changed to store samples as interleaved stereo pair
2021-01-19 Changed filter buffer size to 256 to avoid ring buffer navigation complications
2021-01-19 Tidied up folded filter mechanism before transferring to filter class
2021-01-19 Folded FIR Filter transferred to filter class
2021-01-22 Various chorus test bits and pieces
2021-01-24 Unsuccessful attempts to get variable length sampling working; too difficult to lock into I2S timings
2021-01-24 Reworked chorus mode to use sample buffer in delay routine
2021-01-26 Tidied debug console; added class for fixed IIR filter; refactoring delay
2021-01-26 Reduced FIR tap count; used IIR filter to low pass filter LFO delayed chorus sample
2021-01-27 Minor refactor
2021-01-28 IIIR Filter used to smooth Filter ADC input
2021-01-29 Started updating schematics for new revision
2021-01-31 Added some basic test code for initialising I2C
2021-02-02 I2C DMA Test working with OLED
2021-02-05 Started work on v3 of PCB layout and schematic
2021-02-09 Added some test code using SPI to control Toshiba LED controller
2021-02-11 SPI LED Driver can output all LEDs in sequence
2021-02-12 SPI DMA Tests
2021-02-13 SPI/DMA Led controller working correctly
2021-02-16 Modified LED Handler to use SPI 6 for easier routing (requiring use of BDMA)
2021-02-17 Work on PCB routing
2021-02-17 Completed routing pass of PCB
2021-02-19 Added cycling test mode to RGB LED; Further updates to PCB layout
2021-02-20 PCB Clean up
2021-02-22 Further clean up to PCB; started work on using SPI for WS2812 LEDs
2021-02-25 Updated controls schematic
2021-02-26 Further WS2812 testing
2021-03-02 WS2812 LEDs tested and working
2021-03-03 Updates to panel layout
2021-03-04 Final LED testing - decided on using Toshiba controller as WS2812B approach is very hacky and power inefficient
2021-03-05 Routed controls PCB
2021-03-06 Fix issue where starting chorus mode would result in loud thump
2021-03-07 Updated clock handling for improved accuracy
2021-03-17 Final updates to v2 PCBs for production; USB DFU Mode working
2021-03-19 Removed unnecessary volatiles from delay class
2021-03-19 Removed USB MIDI descriptors; Updated USB serial interface
2021-03-20 Refactoring and class clean up
2021-03-21 Refactoring filter class
2021-03-23 Starting adding Flash save functionality for calibration information
2021-03-24 Further work on config saving/flash functionality
2021-03-25 Startup script now supports multiple bootloaders (STM and custom)
2021-03-25 Added python script to generate wav file containing encoded firmware binary
2021-03-27 First draft of smoothing transitions in python bin to wav script
2021-03-30 Bootloader mechanism can decode audio encoded data (basic implementation with limited error handling)
2021-04-01 Created new project for v2 hardware; Audio ADC working; SDRAM partly working
2021-04-02 Control ADCs, DAC and I2S tested and working with v2 hardware
2021-04-03 Corrections to PCB for v3; implemented filter mode switch
2021-04-03 RGB LED functionality enabled; renamed 'PingPong' mode to 'stereo wide'
2021-04-05 Updated SDRAM to work with 32MB RAM (implemented A12 line); attempts to get SPI DMA working for LED controller
2021-04-07 LED SPI DMA Working
2021-04-07 Tests with filter led
2021-04-08 Started implementing Delay LEDs
2021-04-08 Clean up of delay LED handling
2021-04-09 More work on delay LED handling; started implementing lock button
2021-04-09 Fixed left/right audio input to ADC; tempo lock implemented
2021-04-10 LEDs alter colour according to length of delay
2021-04-11 Various fixes
    * Increase tempo Multiplier times for Long Delay
    * Implement RGB LED functionality for filter types
    * Link button improvements in long delay times
    * Fixes for noise when automating IIR filters
2021-04-11 Tidied up bootloader code
2021-04-13 Started implementing audio test modes
2021-04-13 Config restoration working
2021-04-13 Added audio tests to delay class
2021-04-13 Switched RAM to using CAS latency of 2 for slight performance improvement
2021-04-13 Link button allows right delay to be independent of clock; RAM cleanup
2021-04-15 Debugging ADC issues
2021-04-16 Built tests to assess accuracy of ADC conversions when not using DMA
2021-04-19 Various tests for ADC accuracy
2021-04-20 Refactored ADC handling to improve accuracy of ausio sampling; Added sample gating logic
2021-04-22 Audio ADC conversion triggered once per sample; Further work on gating
2021-04-23 Added option to configure number of FIR taps
2021-04-27 Work on customisable IIR filters
2021-04-28 IIR filters can have number of poles configured
2021-04-28 Filter customisations saving to config
2021-04-28 Updates to LED class
2021-04-30 Backup before removing original chorus mode
2021-05-01 Replaced chorus mechanism with modulated delay using interpolated samples
2021-05-02 Fixed issue where Modulated Delay mode would occasionally crash
2021-05-05 Ongoing work on soft switching filter types
2021-05-06 Clean up of first draft of filter type change soft switching
2021-05-06 Moved soft-switching functionality into filter class - seems to be working well
2021-05-06 Fixes to delay LED handling
2021-05-07 Modulated Delay settings configurable; maximum feedback is 1.1x;
2021-05-07 Started adding support for delay CV controls
2021-05-10 Added some extra USB debug information
2021-05-15 More work on audio bootloader
2021-05-15 Improvements to Audio Bootloader
2021-05-16 Audio bootloader partly working
2021-05-17 Added file version to audio bootloader
2021-05-18 Tweak filter colours
2021-09-23 Cleanup
2022-03-31 Updates to Kicad 6
2024-02-05 Cleaned up hardware folder
2024-10-09 Comment update
2026-04-17 Updated PCB version text
2026-04-20 Removed old Kicad files
2026-05-03 Added debug binaries
2026-05-07 Started setting up new v3 version of firmware
2026-05-15 Cleaning up GPIO code
2026-05-19 Fixed issues with stack in RAM_D1; Updated I2S to send two samples each interrupt
    Moved to DTCMRAM
2026-06-02 Cleaning up bootloader and init code
